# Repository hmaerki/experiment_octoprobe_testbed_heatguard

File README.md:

# experiment_octoprobe_testbed_heatguard
Use octoprobe to test the heatguard for vat pasteurization

## Punchy names for the subsystem

If you want a single, punchy name that sounds professional and captures the "guardian" nature of the device, here are a few proposals categorized by their "vibe":

The Technical Favorites
These sound like official components you would find in an industrial manual:

Thermostop: Clear, concise, and tells you exactly what happens when things go wrong.

Heatguard: Suggests a protective layer standing between the tank and a meltdown.

Safeterm: A portmanteau of "Safety" and "Thermal."

Sentitherm: Combines "Sentinel" (a guard) and "Thermal."

The "Action" Names
These focus on the emergency intervention aspect:

Interlock: The classic engineering term for a system that prevents operation unless specific safety conditions are met.

Cutout: Simple and direct; it describes the physical act of breaking the circuit.

Failsafe: Implies the system is designed to default to a safe state (off) upon error.

The Modern/Sleek Options
If you are naming this for a software module or a branded product:

Pyrowatch: Sounds vigilant and high-tech.

Calyx: (The protective outer part of a flower) — a bit more abstract, but sophisticated.

Vigilant: Short, evocative, and emphasizes the monitoring aspect.

## Punchy names for the application

* Industry	The Problem	The Punchy Name
* Aerospace	Engine overheating	AeroFailsafe
* Nuclear/Energy	Reactor/Boiler runaway	CoreWatch
* Home Automation	Smart water heaters	HomeSentry
* Cryogenics	Warming of liquid nitrogen	FrostGuard

## Industries

1. The Pharmaceutical Industry

In drug manufacturing, "stable" isn't good enough—it must be exact.

* The Application: Water is used in Jacketed Reactors to maintain precise environments for chemical synthesis and in Autoclaves for sterilization.
* The Precision: Often requires accuracy within $\pm 0.5$°C.
* The Risk: If the sensor drifts, the "active pharmaceutical ingredients" (APIs) can degrade, rendering a multi-million dollar batch useless or toxic.
* TPC Punchy Name: BatchGuard2.

2. Food & Beverage (Pasteurization)

Any process involving the "Kill Stage" for bacteria requires a TPC to ensure the temperature never dips too low or spikes too high.

* The Application: Flash Pasteurization of milk, juices, or beer.The Precision: Liquids must be held at a specific temperature (e.g., $72$°C) for a precise number of seconds.
* The Risk: Too low, and you risk a Salmonella outbreak; too high, and the product "cooks" or denatures, ruining the flavor.TPC Punchy Name: PureFlow3. Semiconductor & Electronics ManufacturingThe machines that make computer chips (Photolithography) require incredibly stable thermal environments.
* The Application: Deionized (DI) Water Heating for cleaning silicon wafers.
* The Precision: Thermal fluctuations can cause microscopic expansion or contraction of the wafers, leading to alignment errors in the nanometer range.
* The Risk: Total loss of "yield" (the number of working chips per wafer).
* TPC Punchy Name: NanoSentry

4. Textile & Chemical Dyeing

Color consistency in high-end textiles depends entirely on the temperature of the water bath.

* The Application: Industrial Dye Vats.
* The Precision: Dyes react differently at $79$°C than at $82$°C, causing "color banding."
* The Risk: "Metamerism" (where the color looks different under different lights) or uneven coloring across thousands of meters of fabric.
* TPC Punchy Name: HueLock

5. Modern District Heating (Smart Cities)

Centralized boilers that pump hot water to entire neighborhoods.

* The Application: Hydronic Balancing of large-scale heating loops.
* The Precision: Modern systems use "Predictive Temperature Control" to adjust water heat based on outdoor weather.
* The Risk: A sensor error could lead to "Scald Events" in residential taps or massive energy waste if the boiler over-fires.
* TPC Punchy Name: CitySentry

## Real world products

* https://www.cstainlessllc.com/files/pdfs/vat-pasteurizer-brochure.pdf
* https://www.ancoequipment.com/batch-pasteurizers
* https://pmc.ncbi.nlm.nih.gov/articles/PMC12026572/
  * https://pmc.ncbi.nlm.nih.gov/articles/PMC12026572/table/foods-14-01342-t001/
* https://kalt-ag.ch/en/cheese-vats/
* https://inoxmontagen.ch/produkte/kaesekessel-und-pasteurisatoren/pasteurisator-plevnik-alles-in-einem/
* https://inoxmontagen.ch/produkte/kaesekessel-und-pasteurisatoren/pasteurisatoren-pasteur-plevnik/
* https://www.gea.com/en/products/liquid-processing/pasteurizers/milk-pasteurizer/

## Diagrams about UHT

https://asutp.org/Tetra_Pak/Dairy-Processing-Handbook-Tetrapak.pdf

  * UHT treatment

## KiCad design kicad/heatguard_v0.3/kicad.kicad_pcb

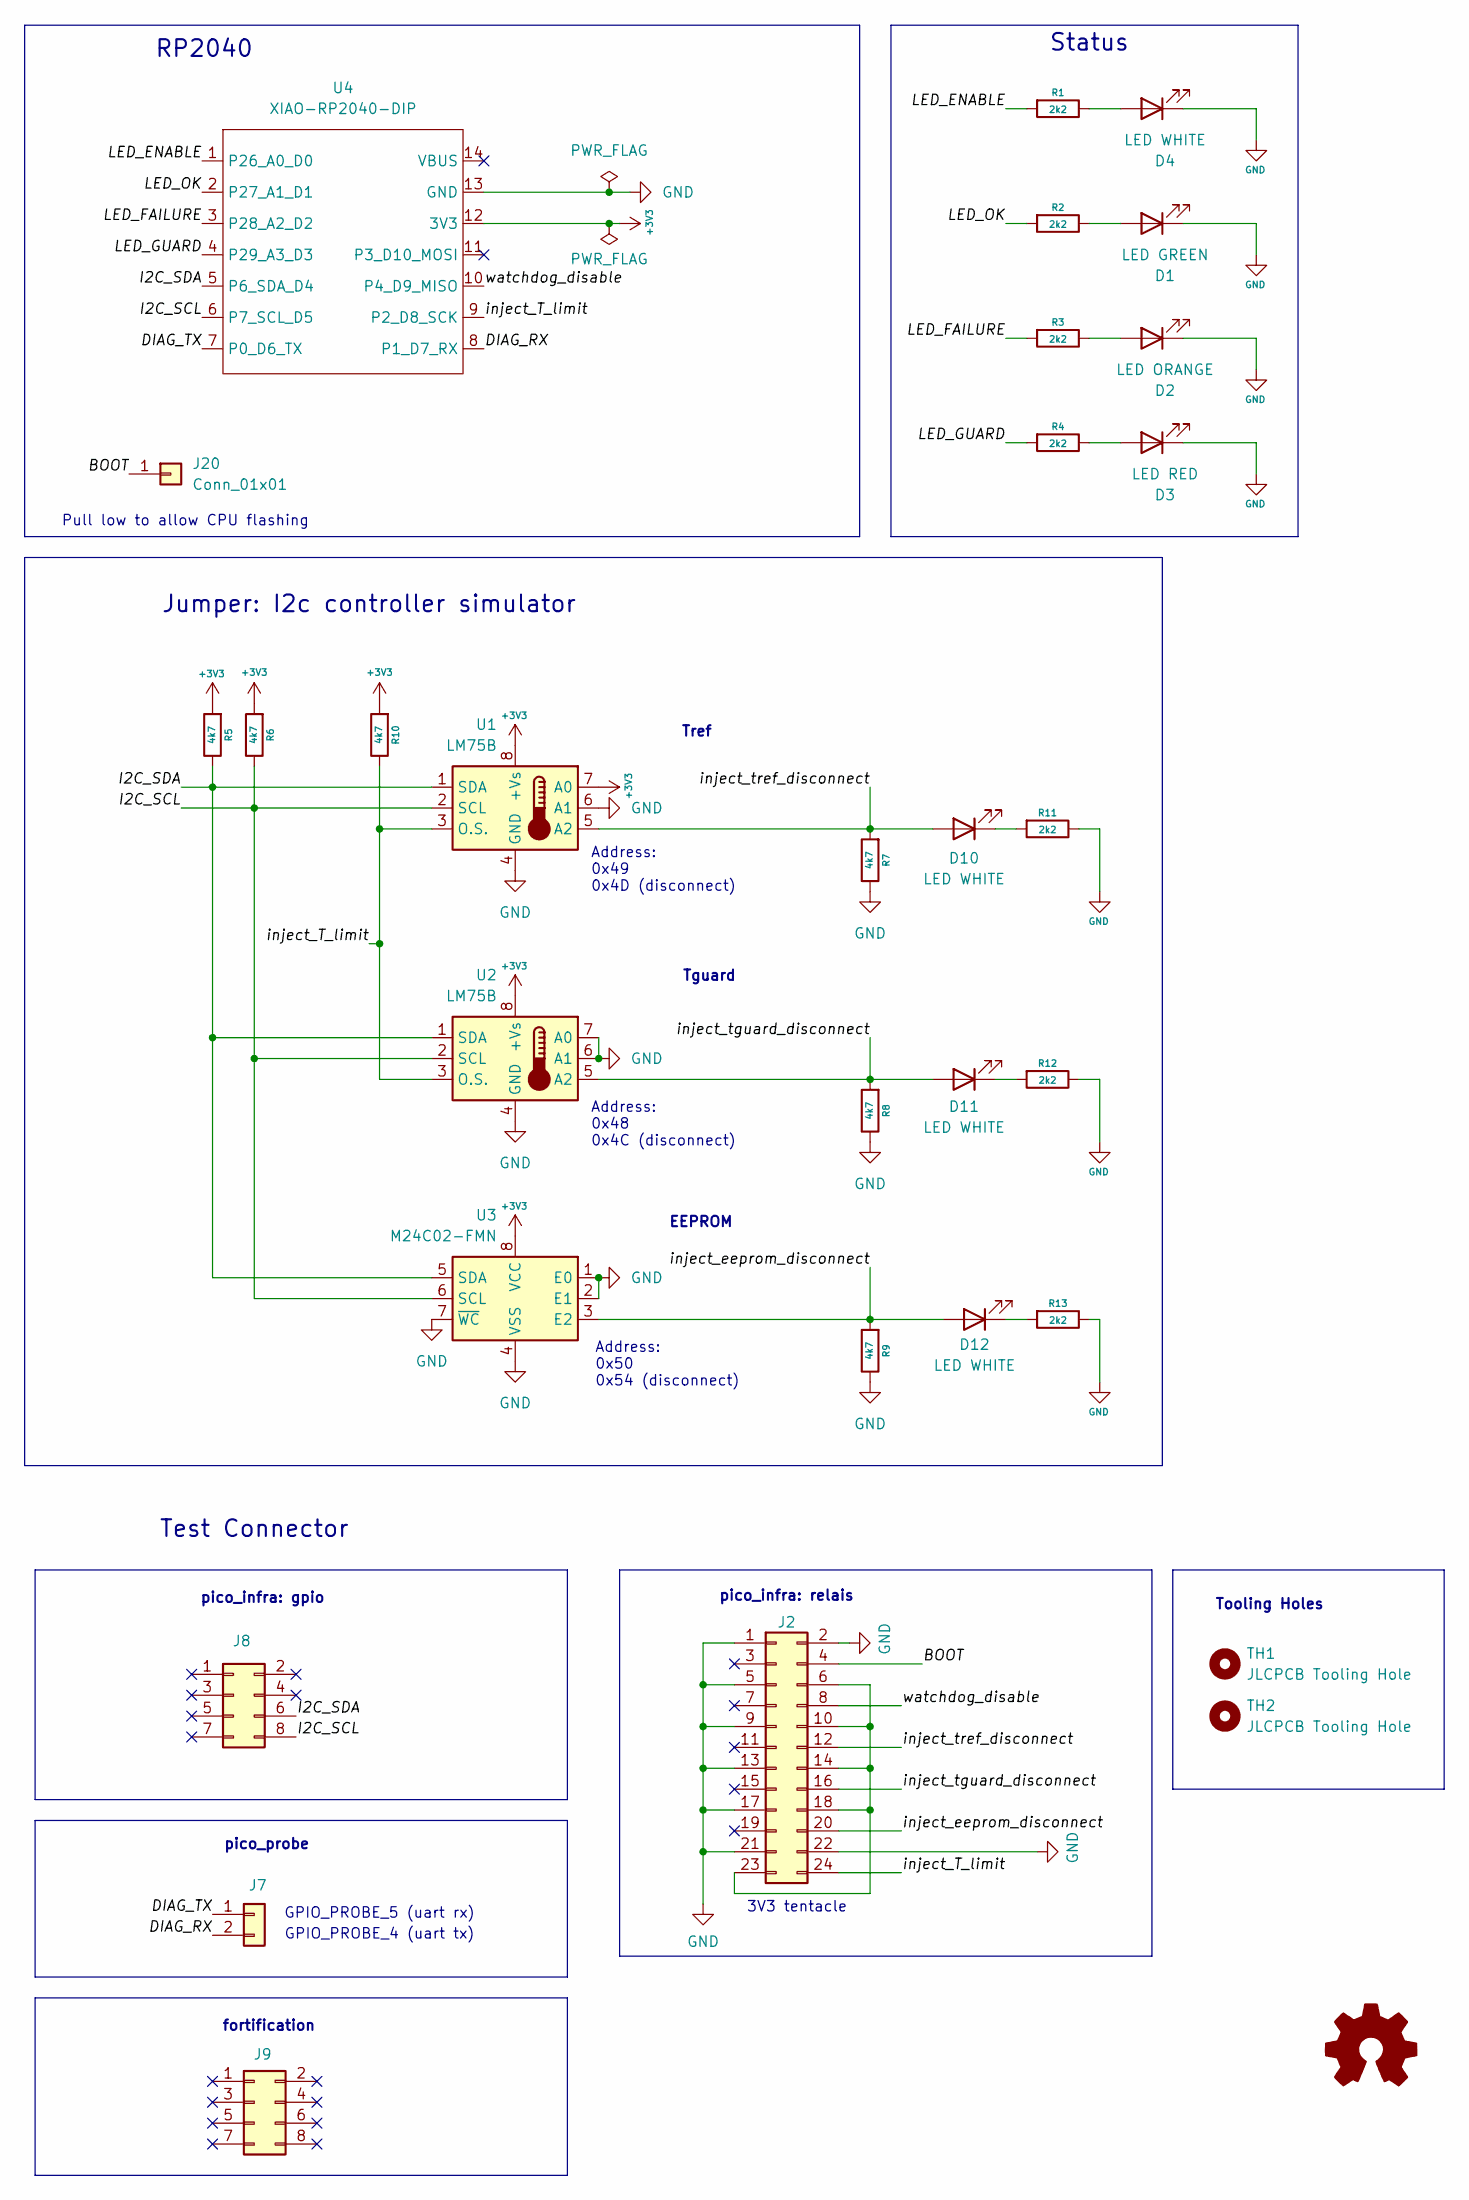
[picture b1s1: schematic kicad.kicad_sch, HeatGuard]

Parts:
D1: LED GREEN; LED_0805_2012Metric; JLC C2297
D2: LED ORANGE; LED_0805_2012Metric; JLC C2296
D3: LED RED; LED_0603_1608Metric; JLC C2286
D4, D10, D11, D12: LED WHITE; LED_0805_2012Metric; JLC C34499
J2: Conn_02x12_Odd_Even; PinHeader_2x12_P2.54mm_Vertical_back
J7: Conn_01x12; PinSocket_1x2_P2.54mm_Vertical_squarepad
J8, J9: Conn_02x04_Odd_Even; PinHeader_2x04_P2.54mm_Vertical_back
J20: Conn_01x01; octoprobe_breakout_PB
Logo_open_hardware101: Logo_Open_Hardware_Small; OSHW-Logo2_9.8x8mm_SilkScreen
R1, R2, R3, R4, R11, R12, R13: 2k2; R_0805_2012Metric_Pad1.20x1.40mm_HandSolder
R5, R6, R7, R8, R9, R10: 4k7; R_0805_2012Metric_Pad1.20x1.40mm_HandSolder
TH1, TH2: JLCPCB Tooling Hole; JLCPCB_ToolingHole
U1, U2: LM75B; SOIC-8_3.9x4.9mm_P1.27mm; JLCPCB C114502
U3: M24C02-FMN; SOIC-8_3.9x4.9mm_P1.27mm; JLCPCB C114502
U4: XIAO-RP2040-DIP

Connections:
+3V3: R5.2, R6.2, R10.2, U1.7 (A0), U1.8 (+Vs), U2.8 (+Vs), U3.8 (VCC), U4.12 (3V3)
/BOOT: J2.4, J20.1
/DIAG_RX: J7.2, U4.8 (P1_D7_RX)
/DIAG_TX: J7.1, U4.7 (P0_D6_TX)
/I2C_SCL: J8.8, R6.1, U1.2 (SCL), U2.2 (SCL), U3.6 (SCL), U4.6 (P7_SCL_D5)
/I2C_SDA: J8.6, R5.1, U1.1 (SDA), U2.1 (SDA), U3.5 (SDA), U4.5 (P6_SDA_D4)
/LED_ENABLE: R1.2, U4.1 (P26_A0_D0)
/LED_FAILURE: R3.2, U4.3 (P28_A2_D2)
/LED_GUARD: R4.2, U4.4 (P29_A3_D3)
/LED_OK: R2.2, U4.2 (P27_A1_D1)
/inject_T_limit: J2.24, R10.1, U1.3 (O.S.), U2.3 (O.S.), U4.9 (P2_D8_SCK)
/inject_eeprom_disconnect: D12.2 (A), J2.20, R9.2, U3.3 (E2)
/inject_tguard_disconnect: D11.2 (A), J2.16, R8.2, U2.5 (A2)
/inject_tref_disconnect: D10.2 (A), J2.12, R7.2, U1.5 (A2)
/watchdog_disable: J2.8, U4.10 (P4_D9_MISO)
GND: D1.1 (K), D2.1 (K), D3.1 (K), D4.1 (K), J2.1, J2.2, J2.5, J2.9, J2.13, J2.17, J2.21, J2.22, R7.1, R8.1, R9.1, R11.1, R12.1, R13.1, U1.4 (GND), U1.6 (A1), U2.4 (GND), U2.6 (A1), U2.7 (A0), U3.1 (E0), U3.2 (E1), U3.4 (VSS), U3.7 (~WC), U4.13 (GND)
unnamed: D1.2 (A), R2.1
unnamed: D2.2 (A), R3.1
unnamed: D3.2 (A), R4.1
unnamed: D4.2 (A), R1.1
unnamed: D10.1 (K), R11.2
unnamed: D11.1 (K), R12.2
unnamed: D12.1 (K), R13.2
unnamed: J2.6, J2.10, J2.14, J2.18, J2.23

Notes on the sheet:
Tooling Holes
Pull low to allow CPU flashing
Status
Test Connector
EEPROM
pico_infra: relais
Tguard
fortification
Address: 0x50 0x54 (disconnect)
RP2040
Tref
GPIO_PROBE_4 (uart tx)
Jumper: I2c controller simulator
GPIO_PROBE_5 (uart rx)
pico_infra: gpio
3V3 tentacle
Address: 0x48 0x4C (disconnect)
Address: 0x49 0x4D (disconnect)
pico_probe

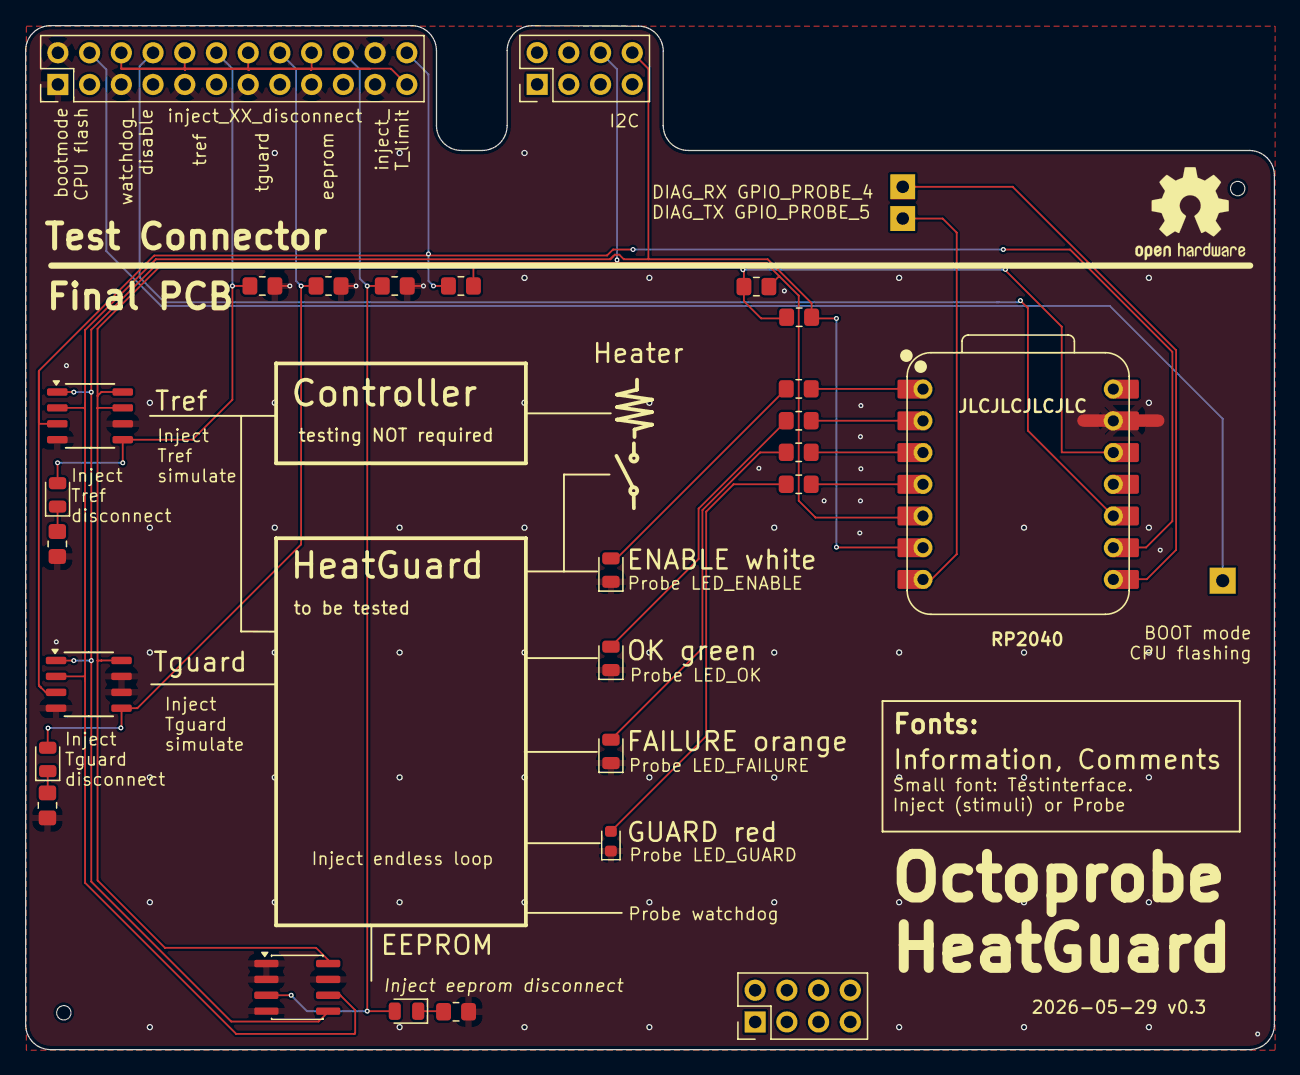
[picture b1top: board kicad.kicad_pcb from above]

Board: 2 copper layers, 100.0 x 82.0 mm, 32 parts (0 on the bottom side), 24 nets.

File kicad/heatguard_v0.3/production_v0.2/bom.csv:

Designator,Footprint,Quantity,Value,LCSC Part #
D1,0805,1,LED GREEN,C2297
"D10, D11, D12, D4",0805,4,LED WHITE,C34499
D2,0805,1,LED ORANGE,C2296
D3,0603,1,LED RED,C2286
"R1, R11, R12, R13, R2, R3, R4",0805,7,2k2,
"R10, R5, R6, R7, R8, R9",0805,6,4k7,
"U1, U2",SOIC-8_3.9x4.9mm_P1.27mm,2,LM75B,
U3,SOIC-8_3.9x4.9mm_P1.27mm,1,M24C02-FMN,

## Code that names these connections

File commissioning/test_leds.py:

import time

import machine

LED_ENABLE = "GPIO26"
LED_OK = "GPIO27"
LED_FAILURE = "GPIO28"
LED_GUARD = "GPIO29"

while True:
    for gpio in (LED_ENABLE, LED_OK, LED_FAILURE, LED_GUARD):
        print(gpio)
        pin = machine.Pin(gpio, machine.Pin.OUT)
        pin.value(1)
        time.sleep(0.5)
        pin.value(0)

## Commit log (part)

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2026-02-24 Expand README with naming proposals and industry applications
    Added section with naming proposals for subsystems and applications across various industries, including technical, action, and modern options.
2026-02-24 v1.0 as ordered
2026-03-16 Now dut-app runs as main.py
2026-03-16 cp heatguard_v01 heatguard_v02
2026-03-16 v0.2: XIAO: Now smd (was on pins)
2026-03-16 v0.2 ready for review
2026-03-17 v0.2 beta
2026-03-17 Remove all vias
2026-03-17 v0.2 as ordered
2026-03-24 Implement uart
2026-03-24 run_sphinx_upload.py
2026-03-25 test_Tguard_high
2026-03-25 Update documentation
2026-03-26 Kicad Schematics A3 -> A4
2026-03-28 debugprobe: power on and get tty
2026-03-28 ruff
2026-03-29 cli: heatguard
2026-03-31 Use uart of PICO_PROBE
2026-04-01 Move .devcontainer in repo directory
2026-04-01 Successful build in devcontainer
2026-04-01 Successfuly run build.sh
2026-04-01 First zephyr implementation by claude
2026-04-01 zephyr version now starts up correctly
2026-04-01 Introduce is_zephyr
2026-04-01 zephyr: Fix watchdog
2026-04-02 heatguard dut-flash now flashes micropython AND zephyr!
2026-05-05 Add doc reference to testbed_CB_JTAG_probe
2026-05-08 Move flash_dut_picotool from testbed_headguard to octoprobe
2026-05-29 Update sphinx
2026-05-29 kicad copy v0.2 -> v0.3
2026-05-29 Changes v0.2 -> v0.3 A
2026-05-30 Changes v0.2 -> v0.3 B: PCB: XIAO rp2040: Replace SMD with THT
2026-05-30 Changes v0.2 -> v0.3 C: Use relays in favor of GPIO
2026-05-30 v0.3: production_v0.3
2026-06-09 Now works on python 3.14.3
2026-06-09 Migrated to PCB v0.3
2026-06-09 PCB stacking: Blue color. Update images with blue color
2026-06-09 Update pin assignements

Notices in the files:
kicad/heatguard_v0.1/kicad.kicad_sch:
Released under MIT Open-source License
